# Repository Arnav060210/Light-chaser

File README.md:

# Light-chaser
Board that makes some lights blink in sequence. 

BOM:

1X NE555P

1X CD4017 

1X Conn01x02Socket / Conn01x01Socket 

1X C_Polarized 

1X C 

2X R 

1X RV

10X LEDS

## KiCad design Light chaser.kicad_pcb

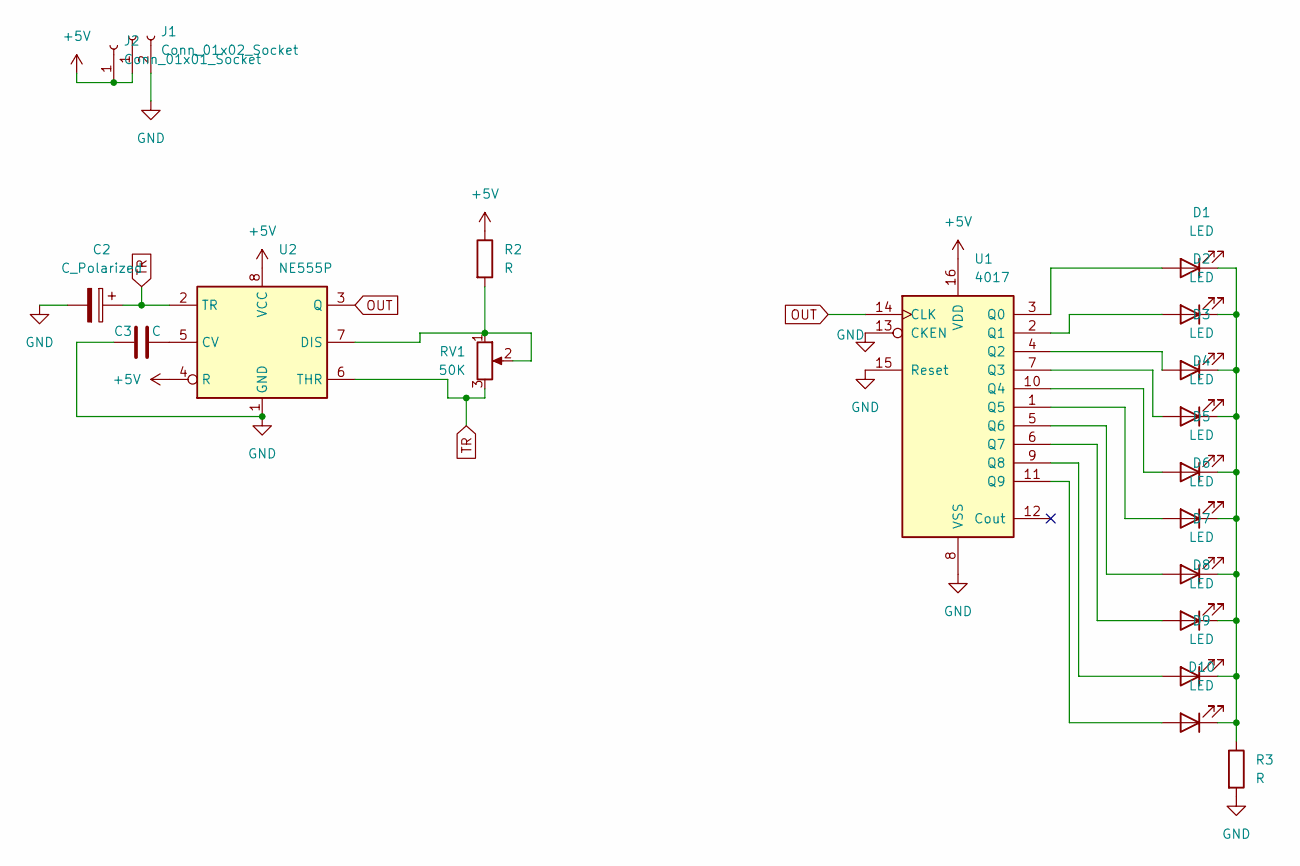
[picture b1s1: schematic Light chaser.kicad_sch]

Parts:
C2: C_Polarized; CP_Radial_D5.0mm_P2.00mm
C3: C; C_Disc_D7.5mm_W2.5mm_P5.00mm
D1, D2, D3, D4, D5, D6, D7, D8, D9, D10: LED; LED_D3.0mm
J1: Conn_01x02_Socket; PinHeader_1x02_P2.54mm_Vertical
J2: Conn_01x01_Socket; PinHeader_1x01_P2.54mm_Vertical
R2, R3: R; R_Axial_DIN0207_L6.3mm_D2.5mm_P7.62mm_Horizontal
RV1: 50K; Potentiometer_Vishay_T93YA_Vertical
U1: 4017; N16
U2: NE555P; DIP-8_W7.62mm

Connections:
+5V: J1.1, J2.1, R2.1, U1.16 (VDD), U2.4 (R), U2.8 (VCC)
GND: C2.2, C3.1, J1.2, R3.2, U1.8 (VSS), U1.13 (CKEN), U1.15 (Reset), U2.1 (GND)
unnamed: D1.2 (A), U1.3 (Q0)
unnamed: D1.1 (K), D2.1 (K), D3.1 (K), D4.1 (K), D5.1 (K), D6.1 (K), D7.1 (K), D8.1 (K), D9.1 (K), D10.1 (K), R3.1
unnamed: D2.2 (A), U1.2 (Q1)
unnamed: D3.2 (A), U1.4 (Q2)
unnamed: D4.2 (A), U1.7 (Q3)
unnamed: D5.2 (A), U1.10 (Q4)
unnamed: D6.2 (A), U1.1 (Q5)
unnamed: D7.2 (A), U1.5 (Q6)
unnamed: D8.2 (A), U1.6 (Q7)
unnamed: D9.2 (A), U1.9 (Q8)
unnamed: D10.2 (A), U1.11 (Q9)
unnamed: C3.2, U2.5 (CV)
unnamed: R2.2, RV1.1, RV1.2, U2.7 (DIS)
OUT: U1.14 (CLK), U2.3 (Q)
TR: C2.1, RV1.3, U2.2 (TR), U2.6 (THR)

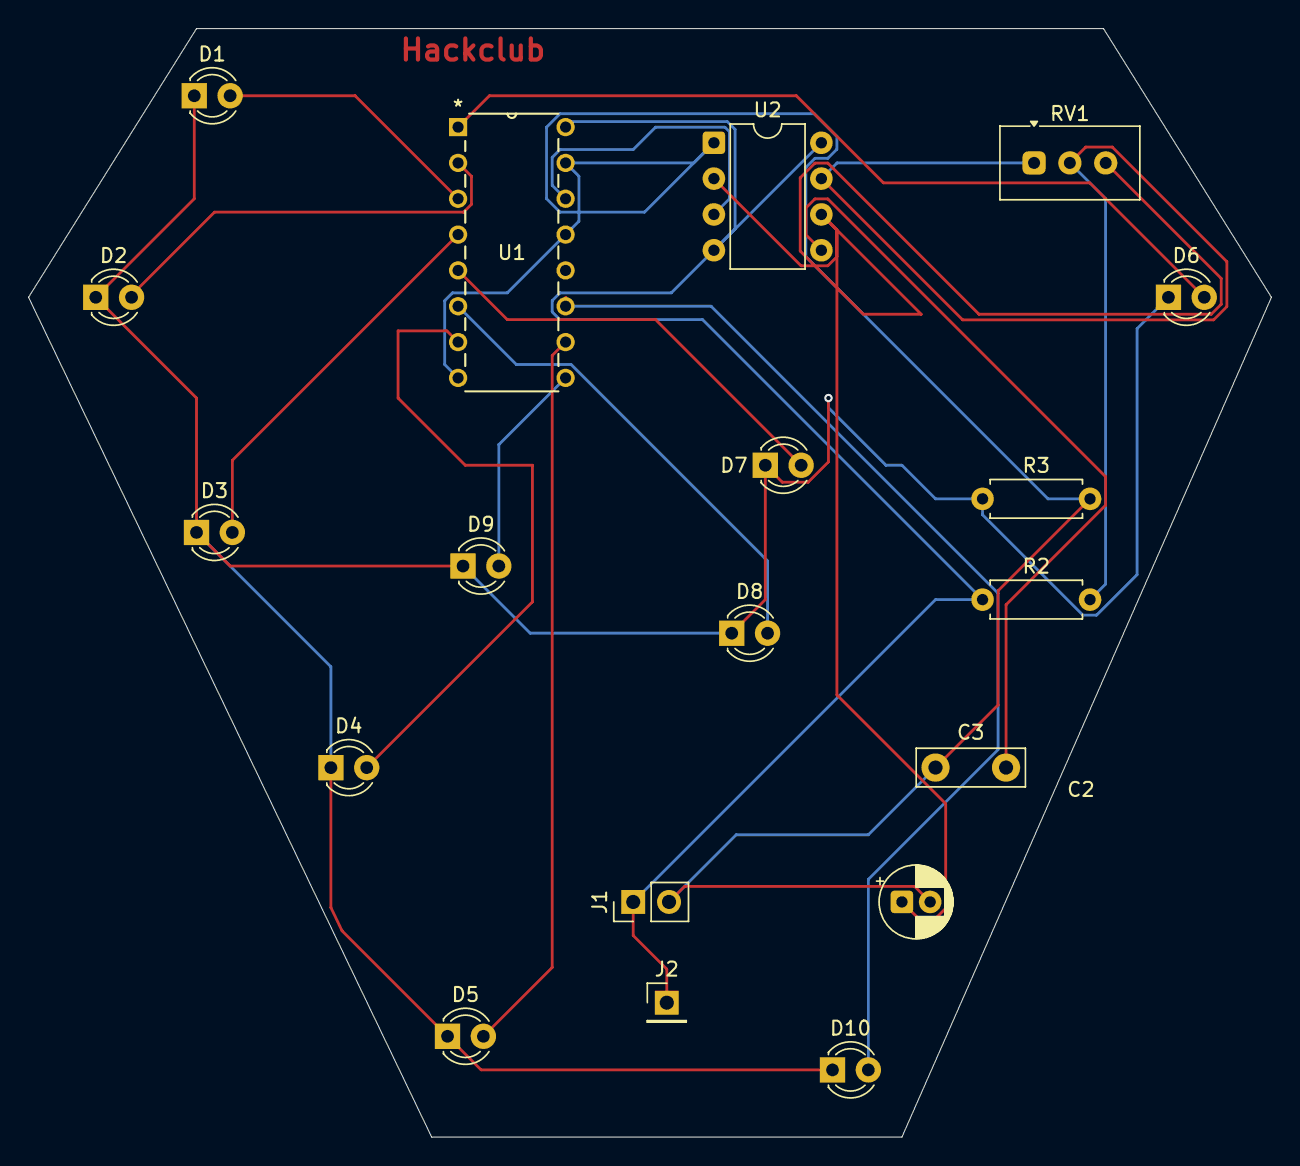
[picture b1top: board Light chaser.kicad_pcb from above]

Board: 2 copper layers, 88.1 x 78.6 mm, 19 parts (0 on the bottom side), 17 nets.

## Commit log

2026-02-26 Create Gerber file
